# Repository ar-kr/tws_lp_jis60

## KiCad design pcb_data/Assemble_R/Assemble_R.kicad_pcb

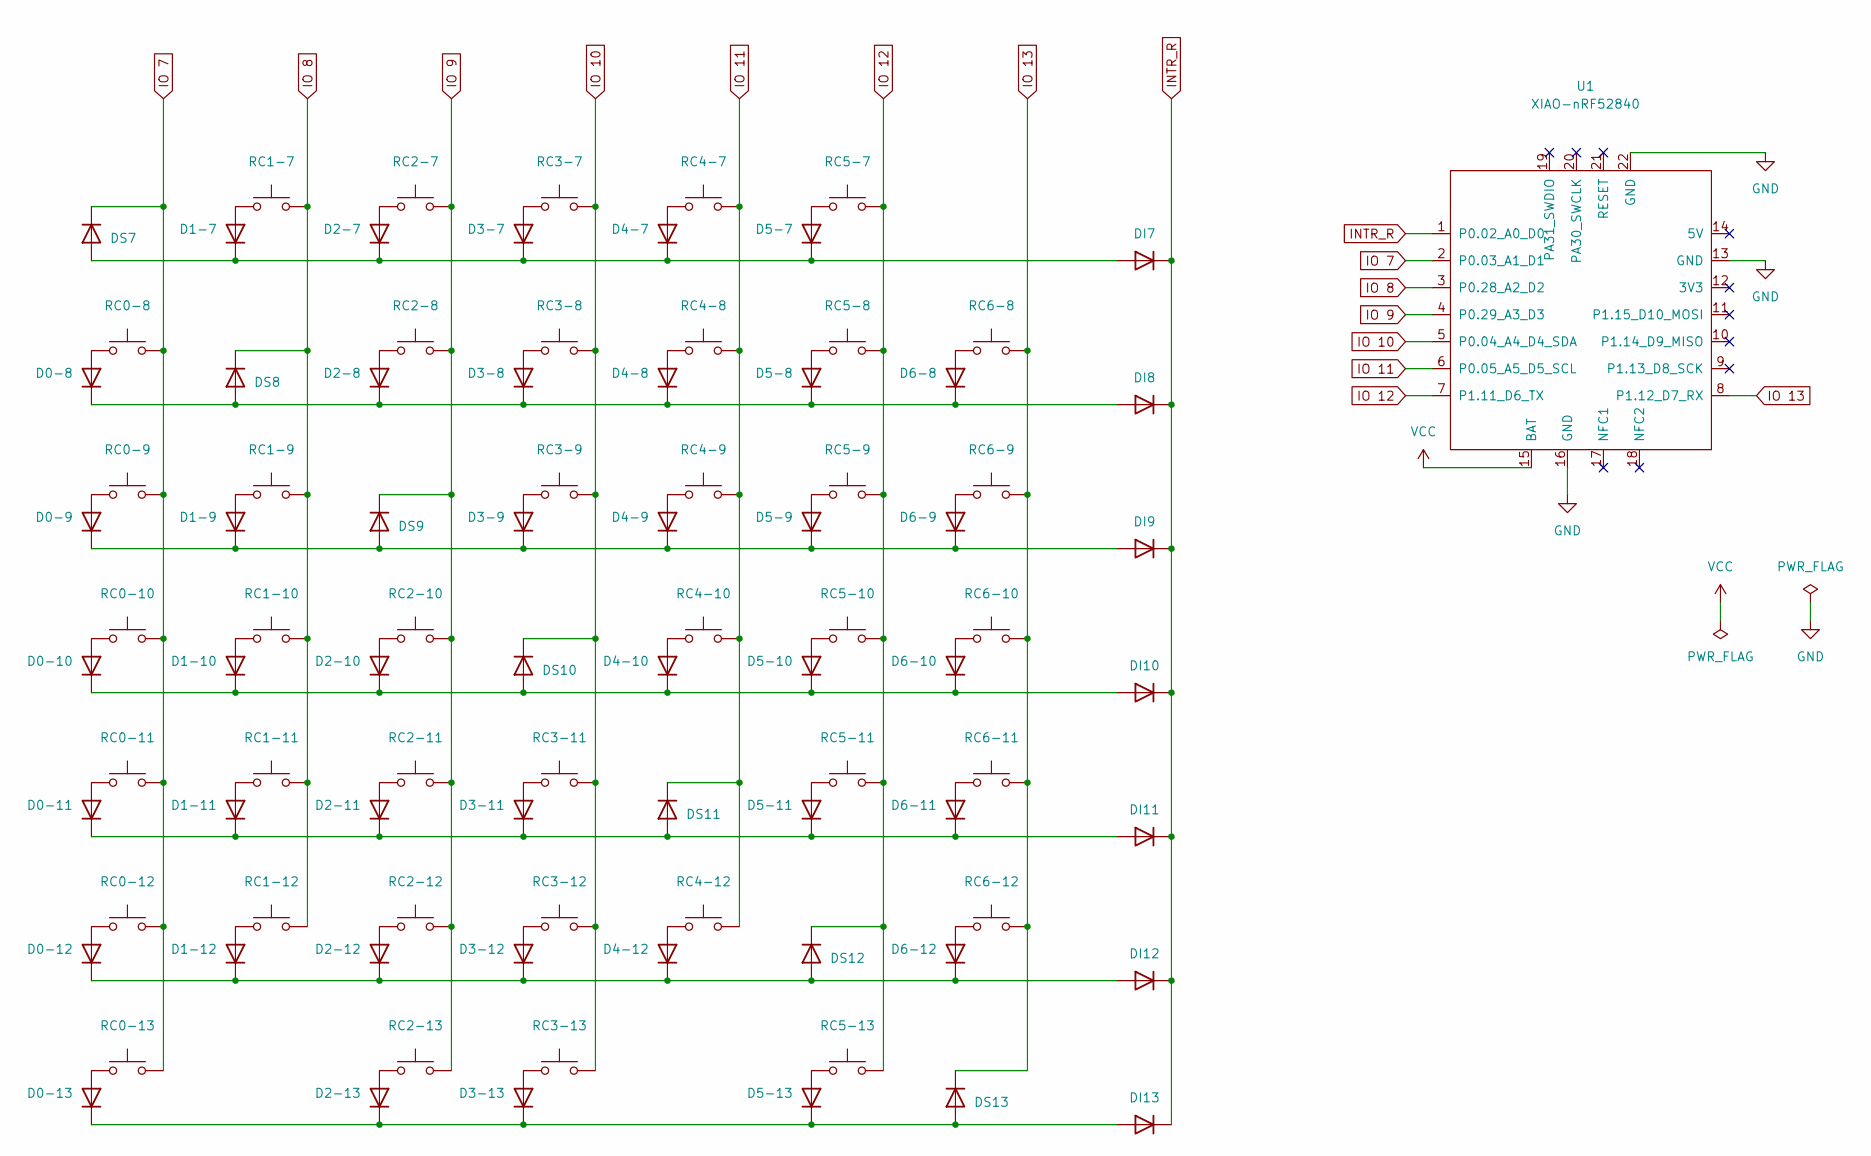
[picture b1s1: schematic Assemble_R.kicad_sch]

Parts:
D0-8, D0-9, D0-10, D0-11, D0-12, D0-13, D1-7, D1-9, D1-10, D1-11, D1-12, D2-7, D2-8, D2-10, D2-11, D2-12, D2-13, D3-7, D3-8, D3-9, D3-11, D3-12, D3-13, D4-7, D4-8, D4-9, D4-10, D4-12, D5-7, D5-8, D5-9, D5-10, D5-11, D5-13, D6-8, D6-9, D6-10, D6-11, D6-12: 1N4148W; Diode_TH_SMD
DI7, DI8, DI9, DI10, DI11, DI12, DI13: 1N4148W; Diode_TH_SMD
DS7, DS8, DS9, DS10, DS11, DS12, DS13: 1N4148W; Diode_TH_SMD
RC0-8, RC0-9, RC0-10, RC0-11, RC0-12, RC1-7, RC1-9, RC1-10, RC1-11, RC1-12, RC2-7, RC2-8, RC2-10, RC2-11, RC2-12, RC2-13, RC3-7, RC3-8, RC3-9, RC3-11, RC3-12, RC3-13, RC4-7, RC4-8, RC4-9, RC4-10, RC4-12, RC5-7, RC5-8, RC5-9, RC5-10, RC5-11, RC5-13, RC6-8, RC6-9, RC6-11, RC6-12: SW_Push; Kailh-PG1353-Hotswap-1U
RC0-13: SW_Push; Kailh-PG1353-Hotswap-1.25U
RC6-10: SW_Push; Kailh-PG1353-Hotswap-ISOEnter
U1: XIAO-nRF52840

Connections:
GND: U1.13 (GND), U1.16 (GND), U1.22 (GND)
INTR_R: DI7.1 (K), DI8.1 (K), DI9.1 (K), DI10.1 (K), DI11.1 (K), DI12.1 (K), DI13.1 (K), U1.1 (P0.02_A0_D0)
IO 7: DS7.1 (K), RC0-8.1, RC0-9.1, RC0-10.1, RC0-11.1, RC0-12.1, RC0-13.1, U1.2 (P0.03_A1_D1)
IO 8: DS8.1 (K), RC1-7.1, RC1-9.1, RC1-10.1, RC1-11.1, RC1-12.1, U1.3 (P0.28_A2_D2)
IO 9: DS9.1 (K), RC2-7.1, RC2-8.1, RC2-10.1, RC2-11.1, RC2-12.1, RC2-13.1, U1.4 (P0.29_A3_D3)
IO 10: DS10.1 (K), RC3-7.1, RC3-8.1, RC3-9.1, RC3-11.1, RC3-12.1, RC3-13.1, U1.5 (P0.04_A4_D4_SDA)
IO 11: DS11.1 (K), RC4-7.1, RC4-8.1, RC4-9.1, RC4-10.1, RC4-12.1, U1.6 (P0.05_A5_D5_SCL)
IO 12: DS12.1 (K), RC5-7.1, RC5-8.1, RC5-9.1, RC5-10.1, RC5-11.1, RC5-13.1, U1.7 (P1.11_D6_TX)
IO 13: DS13.1 (K), RC6-8.1, RC6-9.1, RC6-10.1, RC6-11.1, RC6-12.1, U1.8 (P1.12_D7_RX)
unnamed: D0-8.2 (A), RC0-8.2
unnamed: D0-8.1 (K), D2-8.1 (K), D3-8.1 (K), D4-8.1 (K), D5-8.1 (K), D6-8.1 (K), DI8.2 (A), DS8.2 (A)
unnamed: D0-9.2 (A), RC0-9.2
unnamed: D0-9.1 (K), D1-9.1 (K), D3-9.1 (K), D4-9.1 (K), D5-9.1 (K), D6-9.1 (K), DI9.2 (A), DS9.2 (A)
unnamed: D0-10.2 (A), RC0-10.2
unnamed: D0-10.1 (K), D1-10.1 (K), D2-10.1 (K), D4-10.1 (K), D5-10.1 (K), D6-10.1 (K), DI10.2 (A), DS10.2 (A)
unnamed: D0-11.2 (A), RC0-11.2
unnamed: D0-11.1 (K), D1-11.1 (K), D2-11.1 (K), D3-11.1 (K), D5-11.1 (K), D6-11.1 (K), DI11.2 (A), DS11.2 (A)
unnamed: D0-12.2 (A), RC0-12.2
unnamed: D0-12.1 (K), D1-12.1 (K), D2-12.1 (K), D3-12.1 (K), D4-12.1 (K), D6-12.1 (K), DI12.2 (A), DS12.2 (A)
unnamed: D0-13.2 (A), RC0-13.2
unnamed: D0-13.1 (K), D2-13.1 (K), D3-13.1 (K), D5-13.1 (K), DI13.2 (A), DS13.2 (A)
unnamed: D1-7.2 (A), RC1-7.2
unnamed: D1-7.1 (K), D2-7.1 (K), D3-7.1 (K), D4-7.1 (K), D5-7.1 (K), DI7.2 (A), DS7.2 (A)
unnamed: D1-9.2 (A), RC1-9.2
unnamed: D1-10.2 (A), RC1-10.2
unnamed: D1-11.2 (A), RC1-11.2
unnamed: D1-12.2 (A), RC1-12.2
unnamed: D2-7.2 (A), RC2-7.2
unnamed: D2-8.2 (A), RC2-8.2
unnamed: D2-10.2 (A), RC2-10.2
unnamed: D2-11.2 (A), RC2-11.2
unnamed: D2-12.2 (A), RC2-12.2
unnamed: D2-13.2 (A), RC2-13.2
unnamed: D3-7.2 (A), RC3-7.2
unnamed: D3-8.2 (A), RC3-8.2
unnamed: D3-9.2 (A), RC3-9.2
unnamed: D3-11.2 (A), RC3-11.2
unnamed: D3-12.2 (A), RC3-12.2
unnamed: D3-13.2 (A), RC3-13.2
unnamed: D4-7.2 (A), RC4-7.2
unnamed: D4-8.2 (A), RC4-8.2
unnamed: D4-9.2 (A), RC4-9.2
unnamed: D4-10.2 (A), RC4-10.2
unnamed: D4-12.2 (A), RC4-12.2
unnamed: D5-7.2 (A), RC5-7.2
unnamed: D5-8.2 (A), RC5-8.2
unnamed: D5-9.2 (A), RC5-9.2
unnamed: D5-10.2 (A), RC5-10.2
unnamed: D5-11.2 (A), RC5-11.2
unnamed: D5-13.2 (A), RC5-13.2
unnamed: D6-8.2 (A), RC6-8.2
unnamed: D6-9.2 (A), RC6-9.2
unnamed: D6-10.2 (A), RC6-10.2
unnamed: D6-11.2 (A), RC6-11.2
unnamed: D6-12.2 (A), RC6-12.2
VCC: U1.15 (BAT)

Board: 2 copper layers, 93 parts (38 on the bottom side), 55 nets, no tracks yet.

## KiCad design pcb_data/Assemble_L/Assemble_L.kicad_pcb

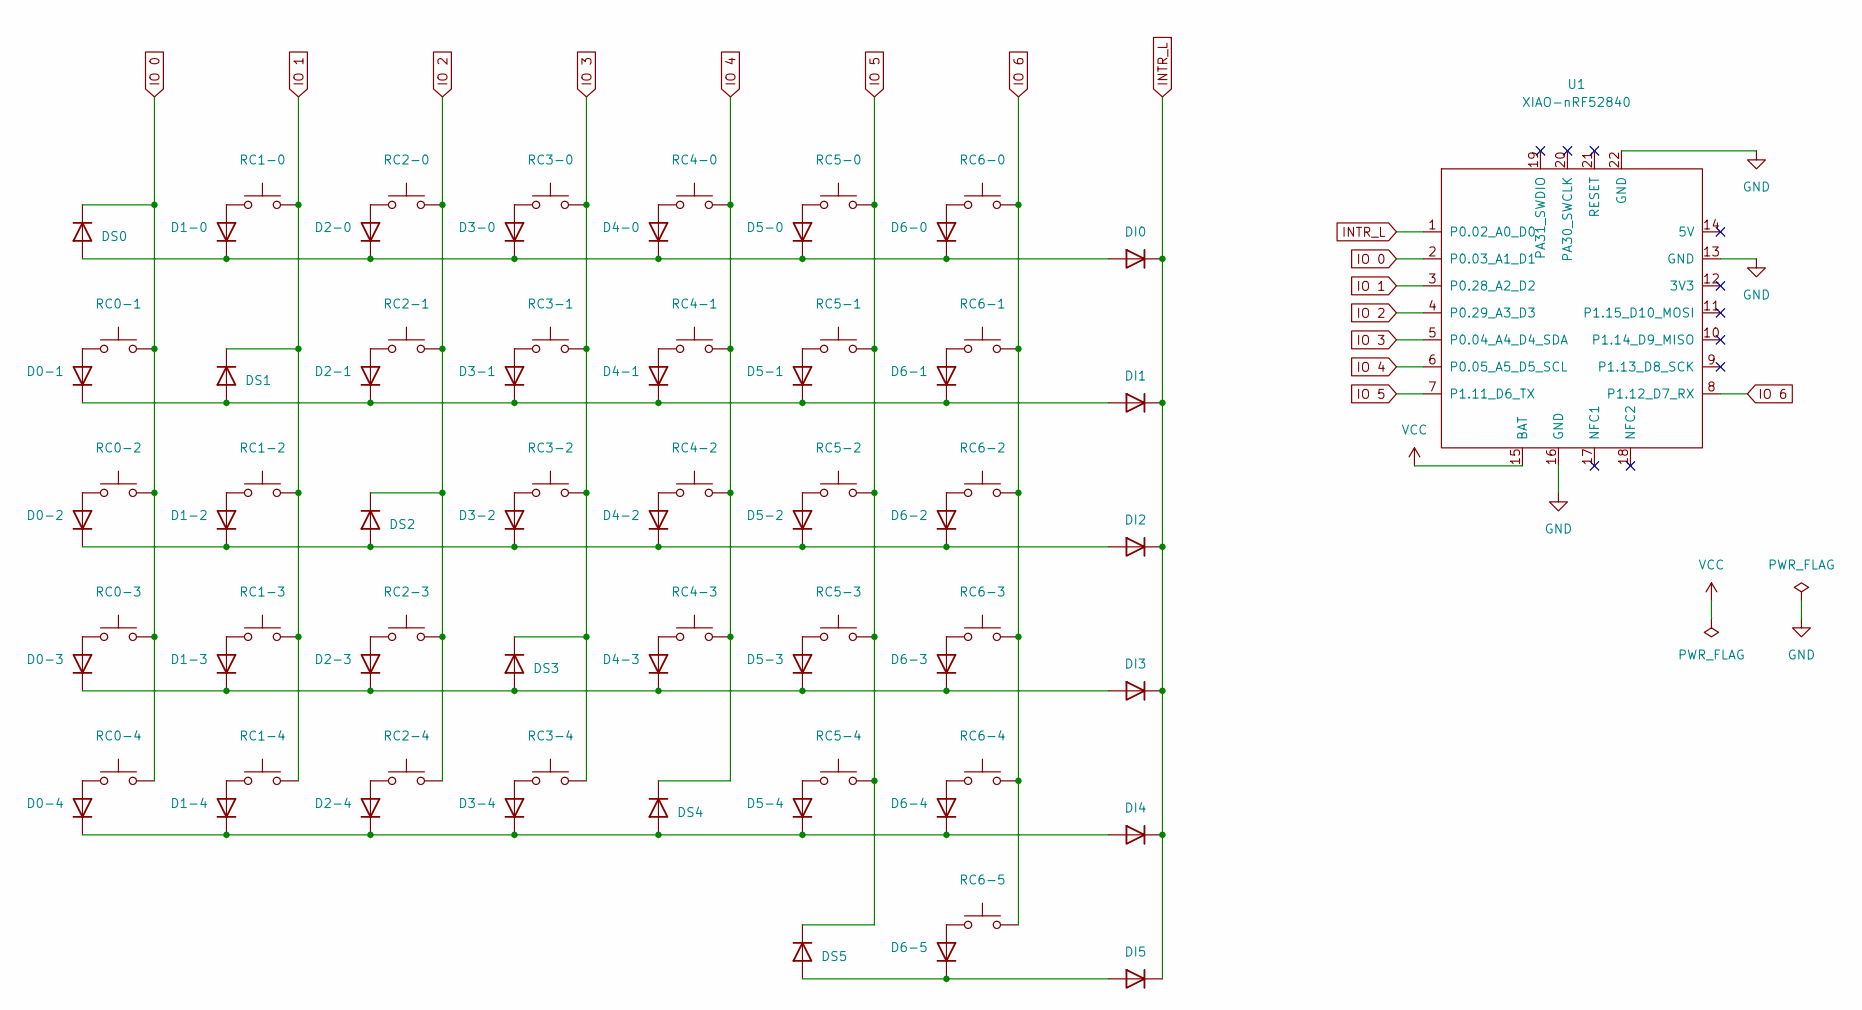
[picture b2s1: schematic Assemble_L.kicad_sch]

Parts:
D0-1, D0-2, D0-3, D0-4, D1-0, D1-2, D1-3, D1-4, D2-0, D2-1, D2-3, D2-4, D3-0, D3-1, D3-2, D3-4, D4-0, D4-1, D4-2, D4-3, D5-0, D5-1, D5-2, D5-3, D5-4, D6-0, D6-1, D6-2, D6-3, D6-4, D6-5: 1N4148W; Diode_TH_SMD
DI0, DI1, DI2, DI3, DI4, DI5: 1N4148W; Diode_TH_SMD
DS0, DS1, DS2, DS3, DS4, DS5: 1N4148W; Diode_TH_SMD
RC0-1: SW_Push; Kailh-PG1353-Hotswap-1.5U
RC0-2: SW_Push; Kailh-PG1353-Hotswap-1.75U
RC0-3: SW_Push; Kailh-PG1353-Hotswap-2U
RC0-4, RC1-0, RC1-2, RC1-3, RC1-4, RC2-0, RC2-1, RC2-3, RC2-4, RC3-0, RC3-1, RC3-2, RC3-4, RC4-0, RC4-1, RC4-2, RC4-3, RC5-0, RC5-1, RC5-2, RC5-3, RC5-4, RC6-0, RC6-1, RC6-2, RC6-3, RC6-4: SW_Push; Kailh-PG1353-Hotswap-1U
RC6-5: SW_Push; Kailh-PG1353-Hotswap-1.25U
U1: XIAO-nRF52840

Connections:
GND: U1.13 (GND), U1.16 (GND), U1.22 (GND)
INTR_L: DI0.1 (K), DI1.1 (K), DI2.1 (K), DI3.1 (K), DI4.1 (K), DI5.1 (K), U1.1 (P0.02_A0_D0)
IO 0: DS0.1 (K), RC0-1.1, RC0-2.1, RC0-3.1, RC0-4.1, U1.2 (P0.03_A1_D1)
IO 1: DS1.1 (K), RC1-0.1, RC1-2.1, RC1-3.1, RC1-4.1, U1.3 (P0.28_A2_D2)
IO 2: DS2.1 (K), RC2-0.1, RC2-1.1, RC2-3.1, RC2-4.1, U1.4 (P0.29_A3_D3)
IO 3: DS3.1 (K), RC3-0.1, RC3-1.1, RC3-2.1, RC3-4.1, U1.5 (P0.04_A4_D4_SDA)
IO 4: DS4.1 (K), RC4-0.1, RC4-1.1, RC4-2.1, RC4-3.1, U1.6 (P0.05_A5_D5_SCL)
IO 5: DS5.1 (K), RC5-0.1, RC5-1.1, RC5-2.1, RC5-3.1, RC5-4.1, U1.7 (P1.11_D6_TX)
IO 6: RC6-0.1, RC6-1.1, RC6-2.1, RC6-3.1, RC6-4.1, RC6-5.1, U1.8 (P1.12_D7_RX)
unnamed: D0-1.2 (A), RC0-1.2
unnamed: D0-1.1 (K), D2-1.1 (K), D3-1.1 (K), D4-1.1 (K), D5-1.1 (K), D6-1.1 (K), DI1.2 (A), DS1.2 (A)
unnamed: D0-2.2 (A), RC0-2.2
unnamed: D0-2.1 (K), D1-2.1 (K), D3-2.1 (K), D4-2.1 (K), D5-2.1 (K), D6-2.1 (K), DI2.2 (A), DS2.2 (A)
unnamed: D0-3.2 (A), RC0-3.2
unnamed: D0-3.1 (K), D1-3.1 (K), D2-3.1 (K), D4-3.1 (K), D5-3.1 (K), D6-3.1 (K), DI3.2 (A), DS3.2 (A)
unnamed: D0-4.2 (A), RC0-4.2
unnamed: D0-4.1 (K), D1-4.1 (K), D2-4.1 (K), D3-4.1 (K), D5-4.1 (K), D6-4.1 (K), DI4.2 (A), DS4.2 (A)
unnamed: D1-0.2 (A), RC1-0.2
unnamed: D1-0.1 (K), D2-0.1 (K), D3-0.1 (K), D4-0.1 (K), D5-0.1 (K), D6-0.1 (K), DI0.2 (A), DS0.2 (A)
unnamed: D1-2.2 (A), RC1-2.2
unnamed: D1-3.2 (A), RC1-3.2
unnamed: D1-4.2 (A), RC1-4.2
unnamed: D2-0.2 (A), RC2-0.2
unnamed: D2-1.2 (A), RC2-1.2
unnamed: D2-3.2 (A), RC2-3.2
unnamed: D2-4.2 (A), RC2-4.2
unnamed: D3-0.2 (A), RC3-0.2
unnamed: D3-1.2 (A), RC3-1.2
unnamed: D3-2.2 (A), RC3-2.2
unnamed: D3-4.2 (A), RC3-4.2
unnamed: D4-0.2 (A), RC4-0.2
unnamed: D4-1.2 (A), RC4-1.2
unnamed: D4-2.2 (A), RC4-2.2
unnamed: D4-3.2 (A), RC4-3.2
unnamed: D5-0.2 (A), RC5-0.2
unnamed: D5-1.2 (A), RC5-1.2
unnamed: D5-2.2 (A), RC5-2.2
unnamed: D5-3.2 (A), RC5-3.2
unnamed: D5-4.2 (A), RC5-4.2
unnamed: D6-0.2 (A), RC6-0.2
unnamed: D6-1.2 (A), RC6-1.2
unnamed: D6-2.2 (A), RC6-2.2
unnamed: D6-3.2 (A), RC6-3.2
unnamed: D6-4.2 (A), RC6-4.2
unnamed: D6-5.2 (A), RC6-5.2
unnamed: D6-5.1 (K), DI5.2 (A), DS5.2 (A)
VCC: U1.15 (BAT)

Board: 2 copper layers, 75 parts (31 on the bottom side), 46 nets, no tracks yet.

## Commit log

2025-11-02 add requirements for board
2025-11-02 add requirements (place holder) for case and assembly
2025-11-16 Add .gitignore
2025-11-16 Add layout file
2025-11-16 temp kicad file
2025-11-18 add library
2025-11-18 temp kicad file (schematic)
2025-11-25 temp
2025-11-25 Add submodule: OPL_Kicad_Library
2025-11-25 Add submodule: MX_V2
2025-11-25 Add submodule: KiCAD_FootPrint
2025-11-25 temp library
2025-11-26 custom footprint
2025-11-26 update symbol
2025-11-28 reset right
2025-11-28 Update right sch
2025-11-28 Update right pcb
